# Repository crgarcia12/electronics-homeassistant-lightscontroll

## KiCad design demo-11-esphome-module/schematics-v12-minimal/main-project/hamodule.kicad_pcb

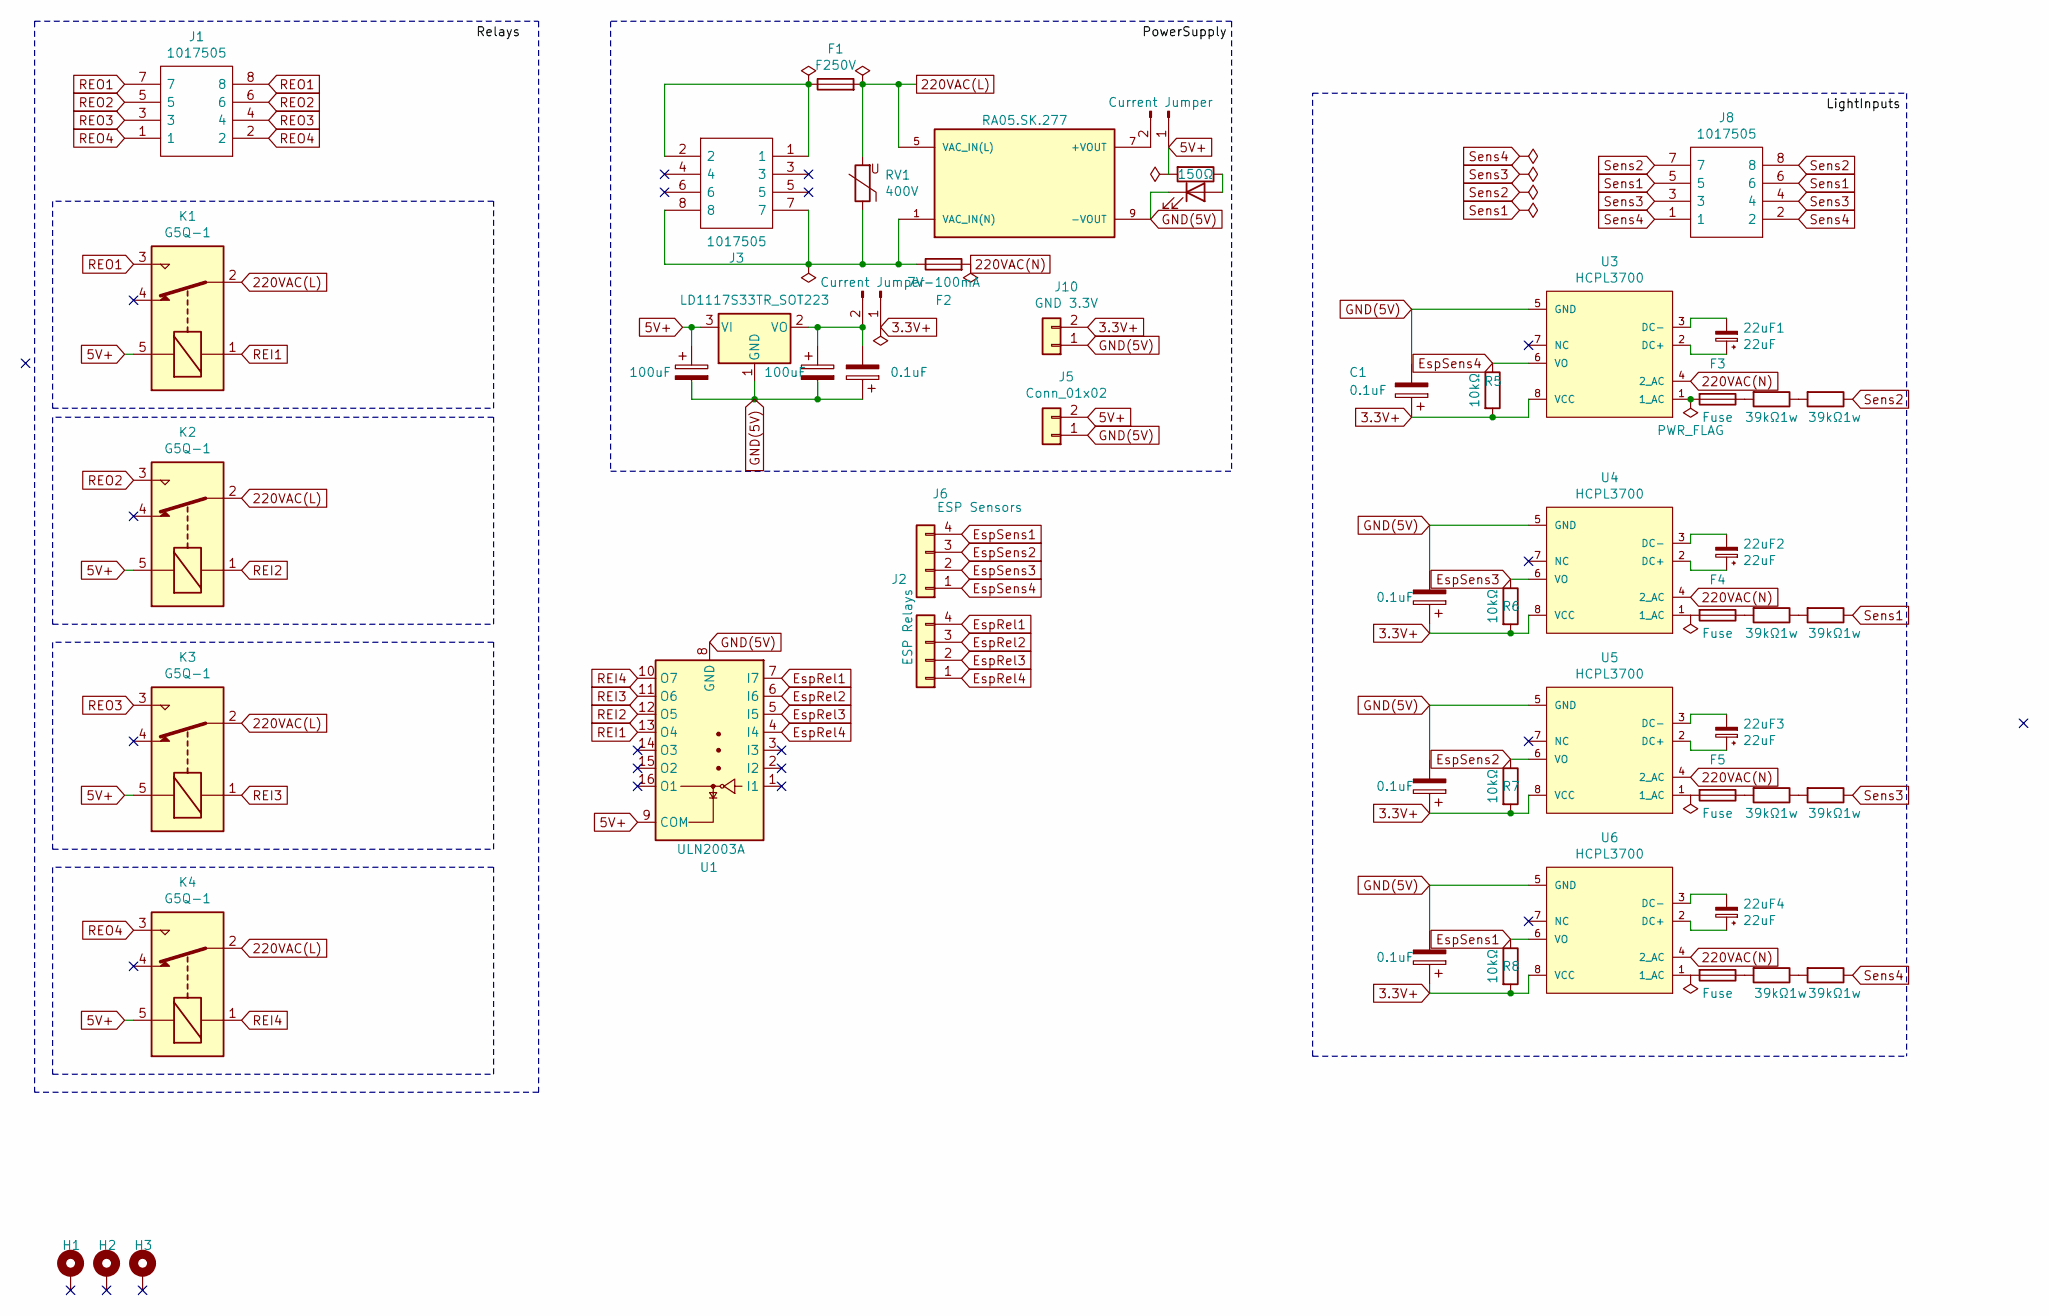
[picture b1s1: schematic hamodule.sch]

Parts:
22uF1, 22uF2, 22uF3, 22uF4: 22uF; CP_EIA-3528-21_Kemet-B_Pad1.50x2.35mm_HandSolder; JLCPCB C110051
100uF_1, 100uF_2: 100uF; CP_Radial_D6.3mm_P2.50mm
C1, C2, C3, C4, C5: 0.1uF; C_0805_2012Metric_Pad1.15x1.40mm_HandSolder; JLCPCB C235777
D9: LED; LED_0805_2012Metric_Pad1.15x1.40mm_HandSolder; JLCPCB C2297
F1: F250V; Fuse_Littelfuse_372_D8.50mm
F2: 7V-100mA; Fuse_Littelfuse_372_D8.50mm
F3, F4, F5, F6: Fuse; Fuse_1812_4532Metric_Pad1.30x3.40mm_HandSolder; JLCPCB C207063
H1, H2, H3: MountingHole_Pad; MountingHole_3.2mm_M3_ISO14580_Pad
J1, J3, J8: 1017505; 1017505_pretty; Manufacturer_Part_Number 1017505; Mouser Part Number 651-1017505
J2: ESP Relays; JST_XH_B4B-XH-A_1x04_P2.50mm_Vertical
J5: Conn_01x02; JST_XH_B2B-XH-A_1x02_P2.50mm_Vertical
J6: ESP Sensors; JST_XH_B4B-XH-A_1x04_P2.50mm_Vertical
J9, J11: Current Jumper; PinHeader_1x02_P2.54mm_Vertical
J10: GND 3.3V; JST_XH_B2B-XH-A_1x02_P2.50mm_Vertical
K1, K2, K3, K4: G5Q-1; Relay_SPDT_Omron-G5Q-1
R5, R6, R7, R8: 10kΩ; R_1206_3216Metric_Pad1.42x1.75mm_HandSolder; JLCPCB C17902
R9: 150Ω; R_0805_2012Metric_Pad1.15x1.40mm_HandSolder; JLCPCB C17471
R10, R11, R12, R13, R14, R15, R16, R17: 39kΩ1w; R_2512_6332Metric_Pad1.52x3.35mm_HandSolder; JLCPCB C25723
RA05.SK.277: RAC05.05SK.277; 277; PARTREV N/A
RV1: 400V; RV_Disc_D12mm_W4.2mm_P7.5mm
U1: ULN2003A; SOIC-16_3.9x9.9mm_P1.27mm; JLCPCB C7512
U2: LD1117S33TR_SOT223; TO-220-3_Vertical
U3, U4, U5, U6: HCPL3700; DIP-8_W7.62mm_Socket_LongPads; Voltage - Isolation 2500Vrms; Voltage - Output (Max) 20V; mouser part number 512-HCPL-3700; digikey description Optoisolator Darlington Output 2500Vrms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

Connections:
3.3V+: C1.1, C2.1, C3.1, C4.1, J10.2, J11.1, R5.2, R6.2, R7.2, R8.2, U3.8 (VCC), U4.8 (VCC), U5.8 (VCC), U6.8 (VCC)
5V+: 100uF_1.1, J5.2, J9.1, K1.5, K2.5, K3.5, K4.5, R9.2, U1.9 (COM), U2.3 (VI); also elsewhere on the board
220VAC(L): F1.2, K1.2, K2.2, K3.2, K4.2, RA05.SK.277.5 (VAC_IN(L)), RV1.2
220VAC(N): F2.2, U3.4 (2_AC), U4.4 (2_AC), U5.4 (2_AC), U6.4 (2_AC)
EspRel1: J2.4, U1.7 (I7)
EspRel2: J2.3, U1.6 (I6)
EspRel3: J2.2, U1.5 (I5)
EspRel4: J2.1, U1.4 (I4)
EspSens1: J6.4, R8.1, U6.6 (VO)
EspSens2: J6.3, R7.1, U5.6 (VO)
EspSens3: J6.2, R6.1, U4.6 (VO)
EspSens4: J6.1, R5.1, U3.6 (VO)
unnamed: 22uF1.1, U3.2 (DC+)
unnamed: 22uF1.2, U3.3 (DC-)
unnamed: 22uF2.1, U4.2 (DC+)
unnamed: 22uF2.2, U4.3 (DC-)
unnamed: 22uF3.1, U5.2 (DC+)
unnamed: 22uF3.2, U5.3 (DC-)
unnamed: 22uF4.1, U6.2 (DC+)
unnamed: 22uF4.2, U6.3 (DC-)
unnamed: D9.2 (A), R9.1
unnamed: F1.1, J3.1, J3.2
unnamed: F2.1, J3.7, J3.8, RA05.SK.277.1 (VAC_IN(N)), RV1.1
unnamed: F3.1, R16.2
unnamed: F3.2, U3.1 (1_AC)
unnamed: F4.1, R14.2
unnamed: F4.2, U4.1 (1_AC)
unnamed: F5.1, R12.2
unnamed: F5.2, U5.1 (1_AC)
unnamed: F6.1, R10.2
unnamed: F6.2, U6.1 (1_AC)
unnamed: J9.2, RA05.SK.277.7 (+VOUT)
unnamed: R10.1, R17.2
unnamed: R11.2, R16.1
unnamed: R12.1, R15.2
unnamed: R13.2, R14.1
REI1: K1.1, U1.13 (O4)
REI2: K2.1, U1.12 (O5)
REI3: K3.1, U1.11 (O6)
REI4: K4.1, U1.10 (O7)
REO1: J1.7, J1.8, K1.3
REO2: J1.5, J1.6, K2.3
REO3: J1.3, J1.4, K3.3
REO4: J1.1, J1.2, K4.3
Sens1: J8.5, J8.6, R13.1
Sens2: J8.7, J8.8, R11.1
Sens3: J8.3, J8.4, R15.1
Sens4: J8.1, J8.2, R17.1

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
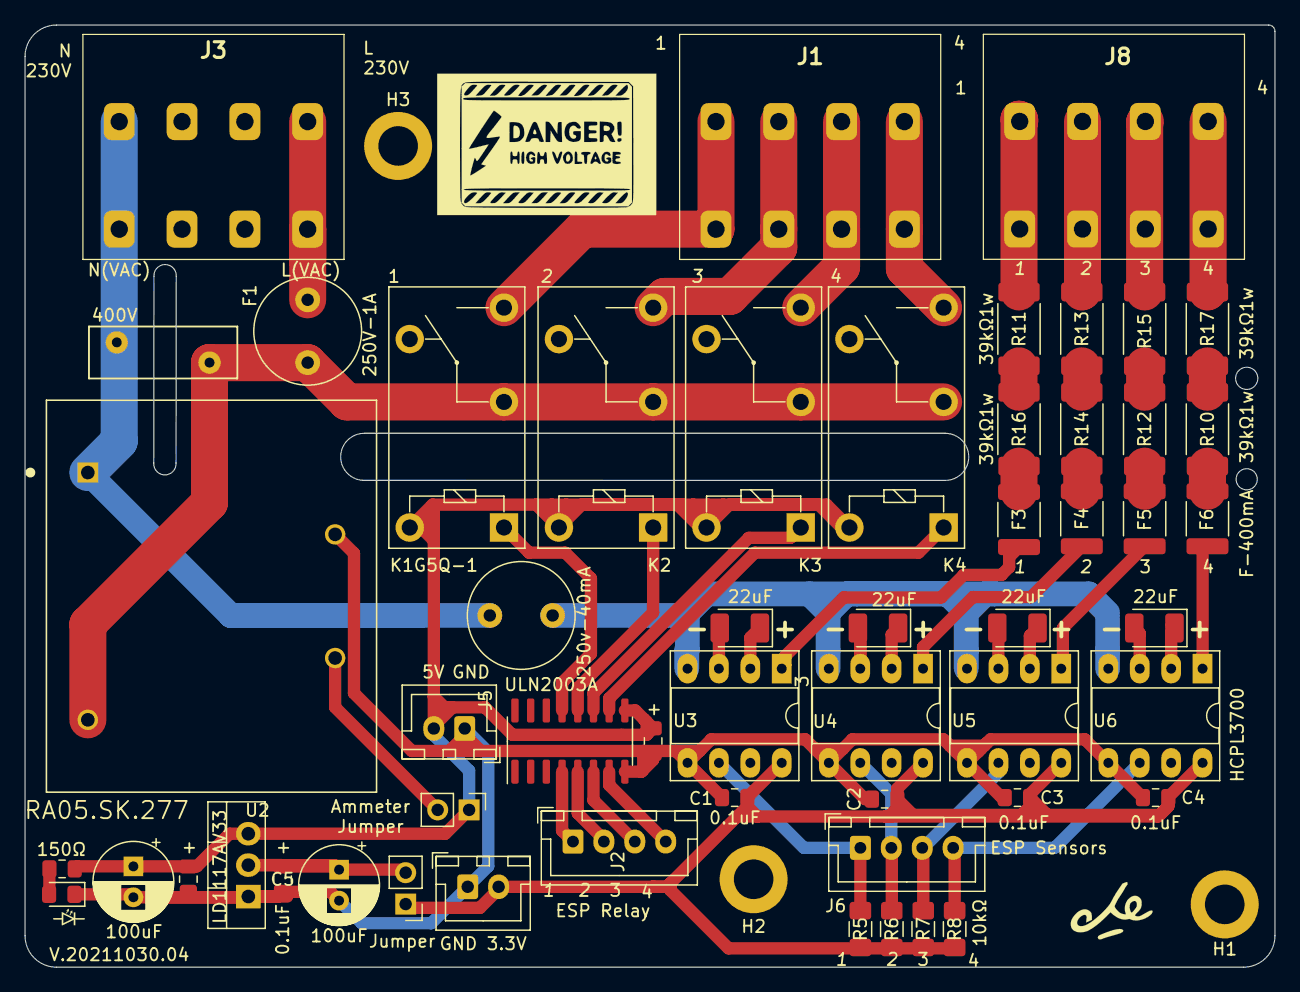
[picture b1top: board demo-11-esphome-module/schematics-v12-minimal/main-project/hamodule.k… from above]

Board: 2 copper layers, 101.1 x 76.2 mm, 57 parts (0 on the bottom side), 50 nets.

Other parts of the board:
C6, C7: 0.1uF; C_0805_2012Metric_Pad1.15x1.40mm_HandSolder

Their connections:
5V+: C6.1, C7.1; also elsewhere on the board

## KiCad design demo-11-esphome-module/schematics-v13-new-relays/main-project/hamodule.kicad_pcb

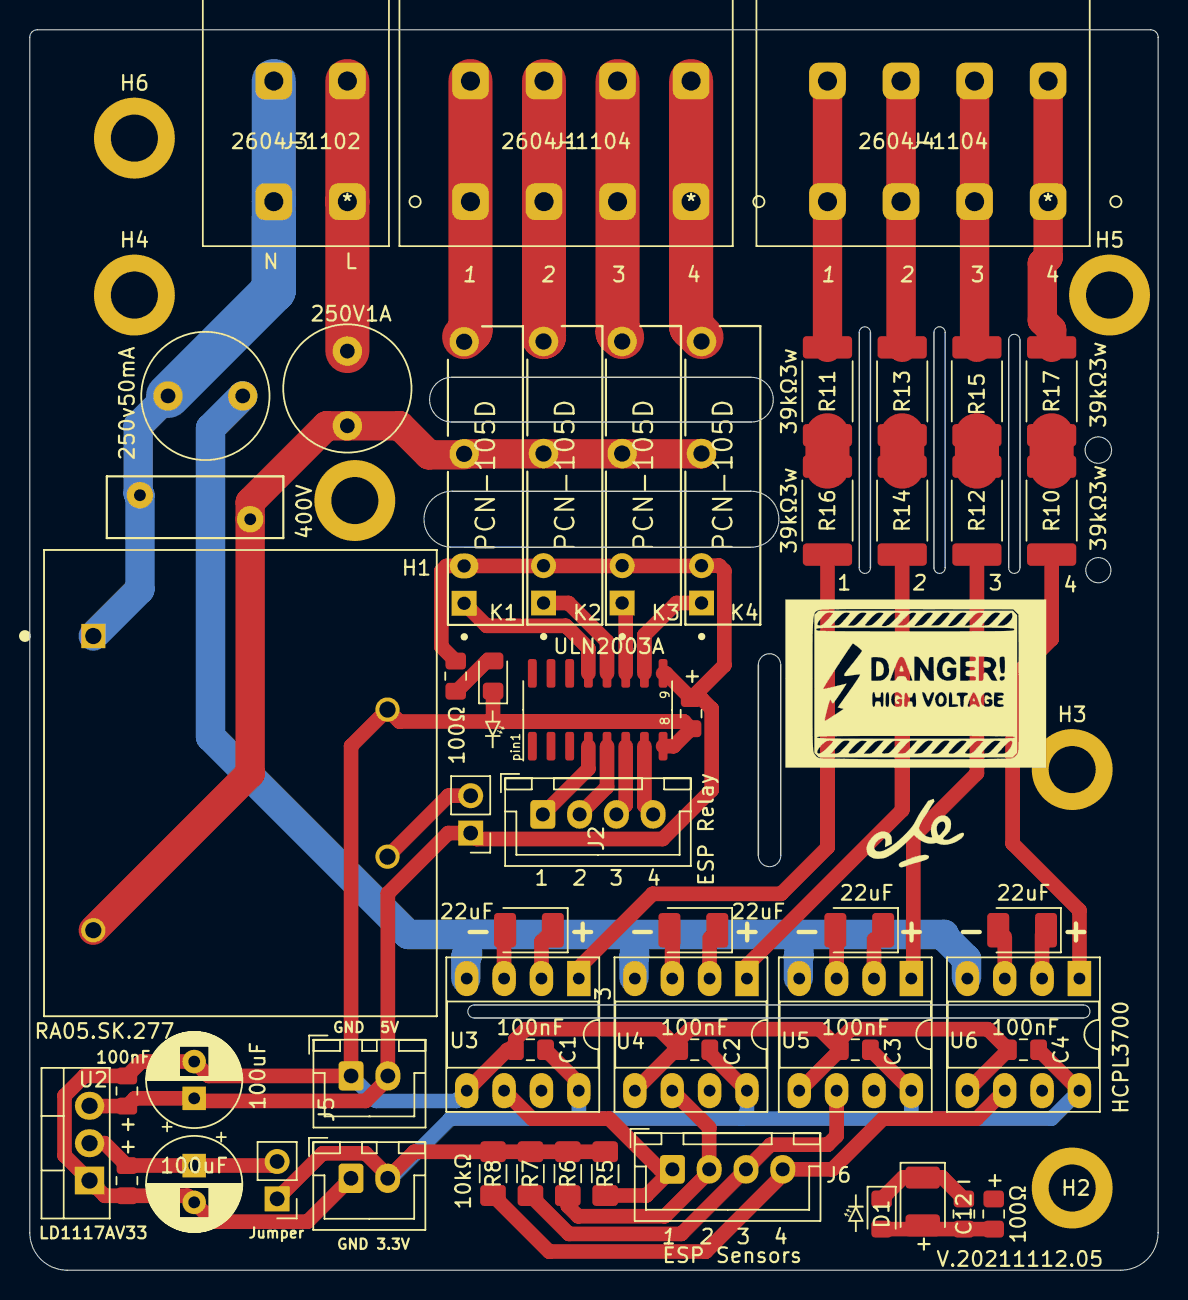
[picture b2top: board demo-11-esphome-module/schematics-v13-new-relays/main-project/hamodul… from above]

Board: 2 copper layers, 76.7 x 84.3 mm, 60 parts (0 on the bottom side), 48 nets.

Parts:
100uF_1, 100uF_2: 100uF; CP_Radial_D6.3mm_P2.50mm
C1, C2, C3, C4, C5, C6, C7, C12: 100nF; C_0805_2012Metric_Pad1.15x1.40mm_HandSolder
C8, C9, C10, C11, C13: 22uF; CP_EIA-3528-21_Kemet-B_Pad1.50x2.35mm_HandSolder
D1, D9: LED; LED_0805_2012Metric_Pad1.15x1.40mm_HandSolder
F1: 250V1A; Fuse_Littelfuse_372_D8.50mm
F2: 250v50mA; Fuse_Littelfuse_372_D8.50mm
H1, H2, H3, H4, H5, H6: MountingHole_Pad; MountingHole_3.2mm_M3_ISO14580_Pad
J1, J4: 2604-1104; big_pads_2604-1104
J2: ESP Relays; JST_XH_B4B-XH-A_1x04_P2.50mm_Vertical
J3: 2604-1102; big_pads_2604-1102
J5: Conn_01x02; JST_XH_B2B-XH-A_1x02_P2.50mm_Vertical
J6: ESP Sensors; JST_XH_B4B-XH-A_1x04_P2.50mm_Vertical
J9, J11: Current Jumper; PinHeader_1x02_P2.54mm_Vertical
J10: GND 3.3V; JST_XH_B2B-XH-A_1x02_P2.50mm_Vertical
K1, K2, K3, K4: PCN-105D; bigpads_TE_Connectivity-PCN-124D
R1, R9: 100Ω; R_0805_2012Metric_Pad1.15x1.40mm_HandSolder
R5, R6, R7, R8: 10kΩ; R_1206_3216Metric_Pad1.42x1.75mm_HandSolder
R10, R11, R12, R13, R14, R15, R16, R17: 39kΩ3w; R_2512_6332Metric_Pad1.52x3.35mm_HandSolder
RA05.SK.277: RAC05.05SK.277; 277
RV1: 400V; RV_Disc_D12mm_W4.2mm_P7.5mm
U1: ULN2003A; SOIC-16_3.9x9.9mm_P1.27mm
U2: LD1117S33TR_SOT223; TO-220-3_Vertical
U3, U4, U5, U6: HCPL3700; DIP-8_W7.62mm_Socket_LongPads

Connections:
3.3V+: C1.1, C2.1, C3.1, C4.1, J10.2, J11.1, R5.2, R6.2, R7.2, R8.2, U3.8, U4.8, U5.8, U6.8
5V+: 100uF_1.1, C6.1, C7.1, J5.2, J9.1, K1.A2, K2.A2, K3.A2, K4.A2, R9.2, U1.9, U2.3
220VAC(L): F1.2, K1.14, K2.14, K3.14, K4.14, RA05.SK.277.5, RV1.2
220VAC(N): F2.2, U3.4, U4.4, U5.4, U6.4
EspRel1: J2.4, U1.7
EspRel2: J2.3, U1.6
EspRel3: J2.2, U1.5
EspRel4: J2.1, U1.4
EspSens1: J6.4, R8.1, U6.6
EspSens2: J6.3, R7.1, U5.6
EspSens3: J6.2, R6.1, U4.6
EspSens4: J6.1, R5.1, U3.6
GND(5V): 100uF_1.2, 100uF_2.2, C1.2, C2.2, C3.2, C4.2, C5.2, C6.2, C7.2, D9.1, J5.1, J10.1, RA05.SK.277.9, U1.8, U2.1, U3.5, U4.5, U5.5, U6.5
L_IN: F1.1, J3.1, J3.2
N_IN: F2.1, J3.3, J3.4, RA05.SK.277.1, RV1.1
unnamed: 100uF_2.1, C5.1, J11.2, U2.2
unnamed: C8.1, U3.2
unnamed: C8.2, U3.3
unnamed: C9.1, U4.2
unnamed: C9.2, U4.3
unnamed: C10.1, U5.2
unnamed: C10.2, U5.3
unnamed: C11.1, U6.2
unnamed: C11.2, U6.3
unnamed: C12.1, C13.2, D1.2, R1.1
unnamed: C12.2, C13.1, D1.1
unnamed: D9.2, R9.1
unnamed: J9.2, RA05.SK.277.7
unnamed: R10.1, R17.2
unnamed: R10.2, U6.1
unnamed: R11.2, R16.1
unnamed: R12.1, R15.2
unnamed: R12.2, U5.1
unnamed: R13.2, R14.1
unnamed: R14.2, U4.1
unnamed: R16.2, U3.1
REI1: K1.A1, U1.13
REI2: K2.A1, U1.12
REI3: K3.A1, U1.11
REI4: K4.A1, U1.10
REO1: J1.7, J1.8, K1.11
REO2: J1.5, J1.6, K2.11
REO3: J1.3, J1.4, K3.11
REO4: J1.1, J1.2, K4.11
Sens1: J4.7, J4.8, R11.1
Sens2: J4.5, J4.6, R13.1
Sens3: J4.3, J4.4, R15.1
Sens4: J4.1, J4.2, R17.1

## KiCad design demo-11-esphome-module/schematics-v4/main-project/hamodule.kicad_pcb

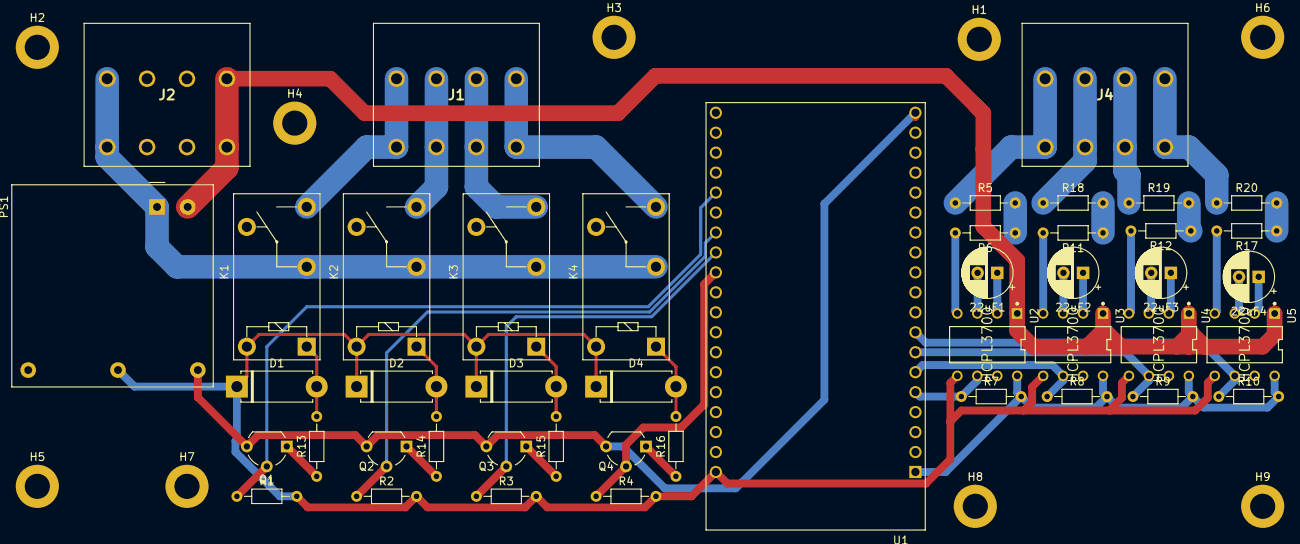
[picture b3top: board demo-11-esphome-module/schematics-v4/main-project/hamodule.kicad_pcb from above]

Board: 2 copper layers, 54 parts (0 on the bottom side), 46 nets.

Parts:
22uF1, 22uF2, 22uF3, 22uF4: CP_Small; CP_Radial_D6.3mm_P2.50mm
D1, D2, D3, D4: DIODE; D_5W_P10.16mm_Horizontal
H1, H2, H3, H4, H5, H6, H7, H8, H9: MountingHole_Pad; MountingHole_3.2mm_M3_ISO14580_Pad
J1, J2, J4: 1017505
K1, K2, K3, K4: G5Q-1; Relay_SPDT_Omron-G5Q-1
PS1: RAC05-05SK; Converter_ACDC_RECOM_RAC05-xxSK_THT
Q1, Q2, Q3, Q4: 2N2219; TO-92_Wide
R1, R2, R3, R4, R7, R8, R9, R10: 10K; R_Axial_DIN0204_L3.6mm_D1.6mm_P7.62mm_Horizontal
R5, R6, R11, R12, R17, R18, R19, R20: 47k; R_Axial_DIN0204_L3.6mm_D1.6mm_P7.62mm_Horizontal
R13, R14, R15, R16: 220; R_Axial_DIN0204_L3.6mm_D1.6mm_P7.62mm_Horizontal
U1: ESP32-DEVKITC-32D; MODULE_ESP32-DEVKITC-32D
U2, U3, U4, U5: HCPL3700; ON_Semi-CASE_62605_ISSUE_P-0-0-0

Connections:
3.3V+: R7.2, R8.2, R9.2, R10.2, U1.1, U2.8, U3.8, U4.8, U5.8
5V+: PS1.5, Q1.3, Q2.3, Q3.3, Q4.3, U1.19
5VGND: D1.1, D2.1, D3.1, D4.1, K1.5, K2.5, K3.5, K4.5, PS1.4, R1.2, R2.2, R3.2, R4.2, U1.20, U2.5, U3.5, U4.5, U5.5
220VAC(L): J2.7, J2.8, K1.2, K2.2, K3.2, K4.2, PS1.1
220VAC(N): J2.1, J2.2, PS1.2, U2.1, U3.1, U4.1, U5.1
Earth: H1.1, H2.1, H3.1, H4.1, H5.1, H6.1, H7.1, H8.1, H9.1, J2.3, J2.4, J2.5, J2.6
GPIO32: R9.1, U1.7, U4.6
GPIO33: R10.1, U1.8, U5.6
GPIO34: R7.1, U1.5, U2.6
GPIO35: R8.1, U1.6, U3.6
unnamed: 22uF1.1, U2.2
unnamed: 22uF1.2, U2.3
unnamed: 22uF2.1, U3.2
unnamed: 22uF2.2, U3.3
unnamed: 22uF3.1, U4.2
unnamed: 22uF3.2, U4.3
unnamed: 22uF4.1, U5.2
unnamed: 22uF4.2, U5.3
unnamed: D1.2, K1.1, R13.2
unnamed: D2.2, K2.1, R14.2
unnamed: D3.2, K3.1, R15.2
unnamed: D4.2, K4.1, R16.2
unnamed: Q1.1, R13.1
unnamed: Q1.2, R1.1, U1.34
unnamed: Q2.1, R14.1
unnamed: Q2.2, R2.1, U1.32
unnamed: Q3.1, R15.1
unnamed: Q3.2, R3.1, U1.31
unnamed: Q4.1, R16.1
unnamed: Q4.2, R4.1, U1.30
unnamed: R5.2, R6.1
unnamed: R6.2, U2.4
unnamed: R11.1, R18.2
unnamed: R11.2, U3.4
unnamed: R12.1, R19.2
unnamed: R12.2, U4.4
unnamed: R17.1, R20.2
unnamed: R17.2, U5.4
REO1: J1.7, J1.8, K1.3
REO2: J1.5, J1.6, K2.3
REO3: J1.3, J1.4, K3.3
REO4: J1.1, J1.2, K4.3
Sens1: J4.7, J4.8, R5.1
Sens2: J4.5, J4.6, R18.1
Sens3: J4.3, J4.4, R19.1
Sens4: J4.1, J4.2, R20.1

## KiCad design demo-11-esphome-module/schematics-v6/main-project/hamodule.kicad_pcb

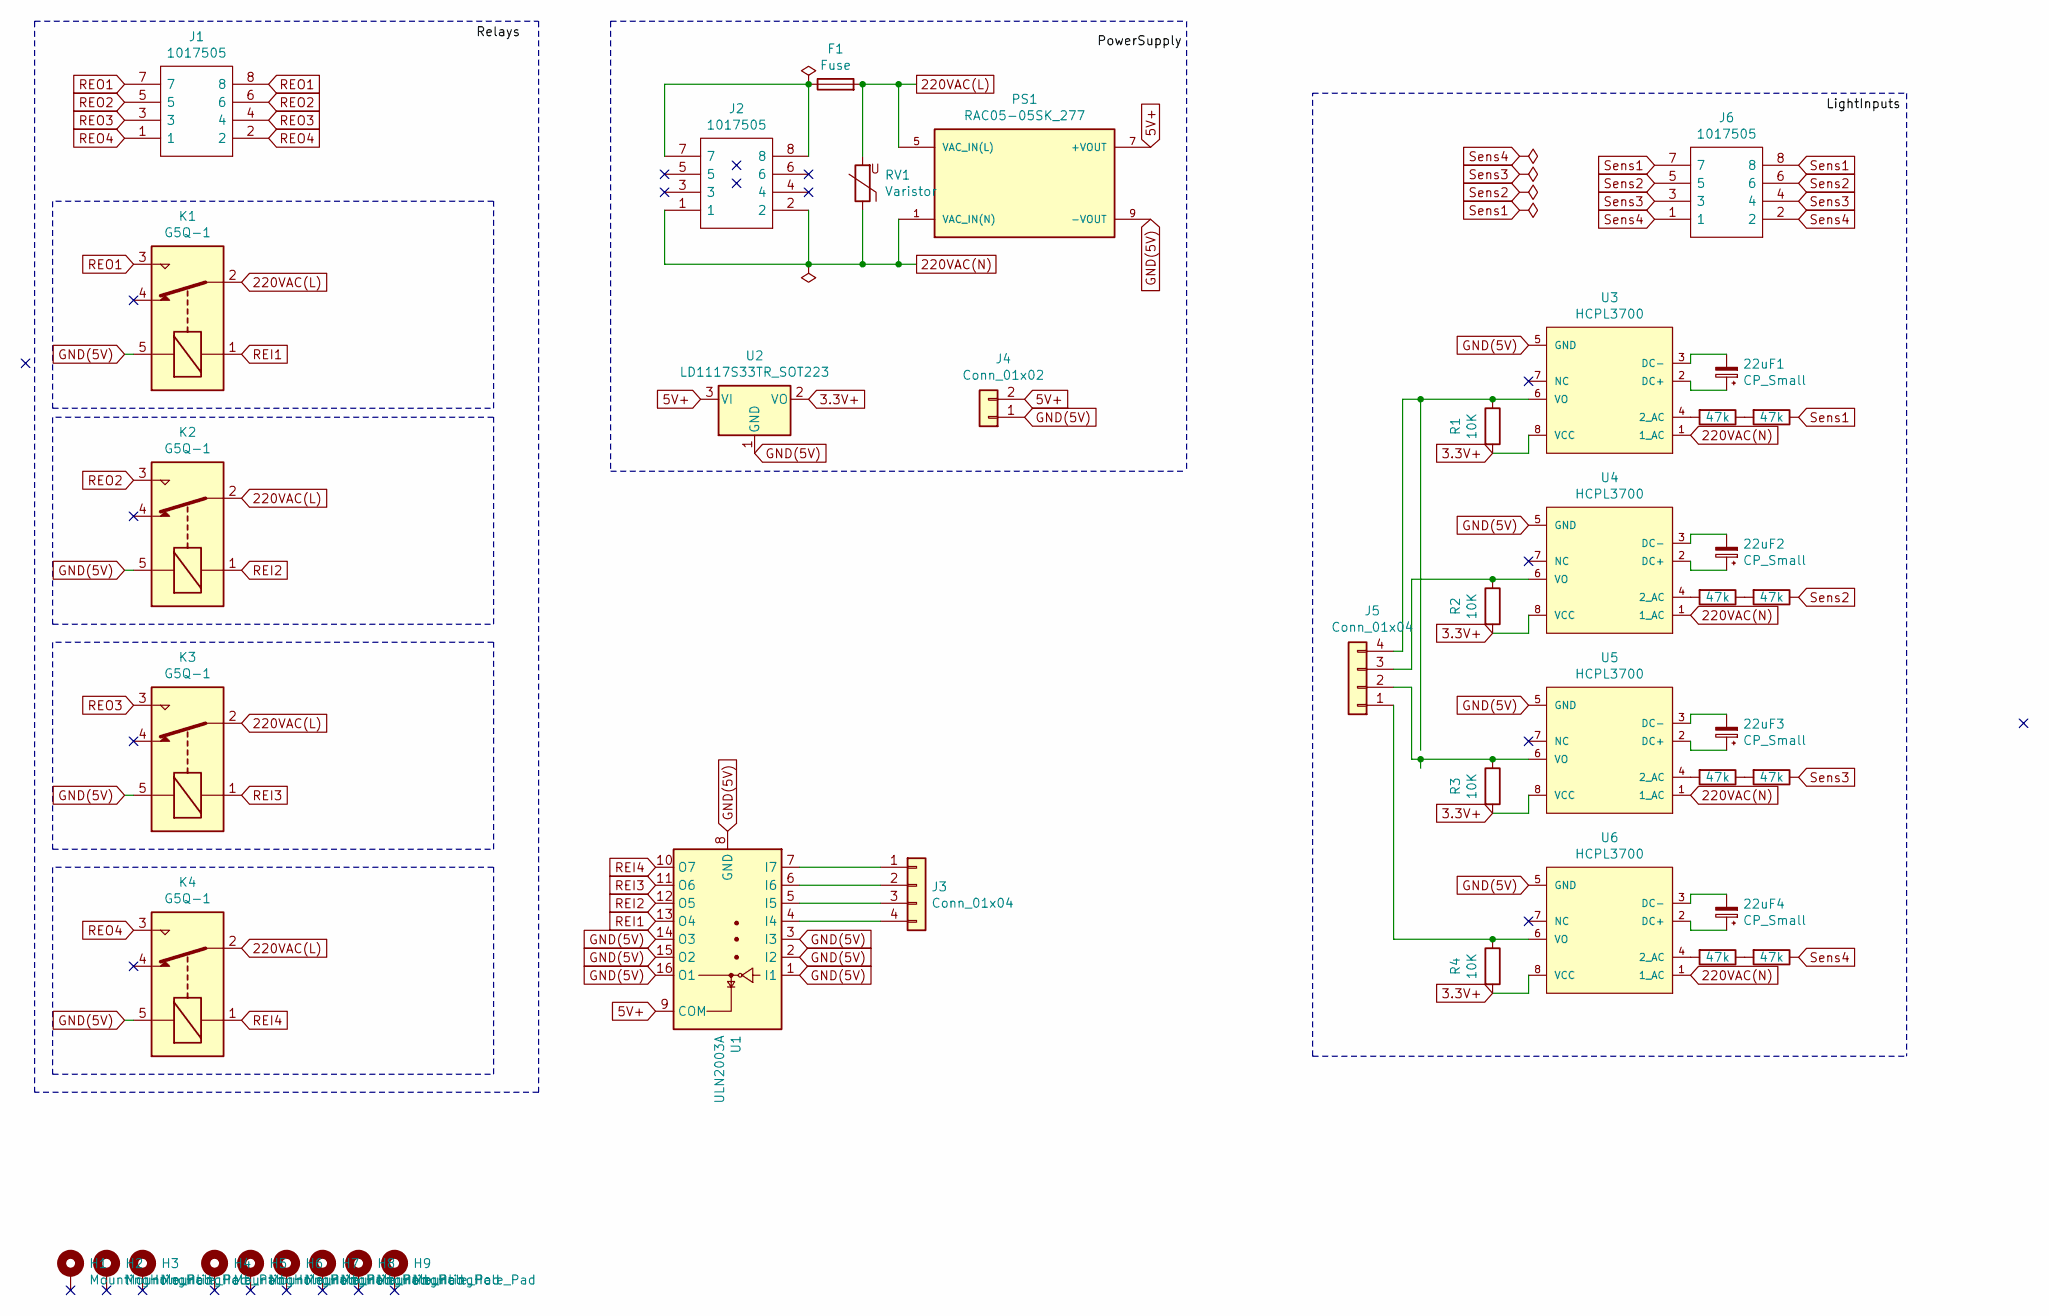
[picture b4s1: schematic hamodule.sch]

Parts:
22uF1, 22uF2, 22uF3, 22uF4: CP_Small; CP_Radial_D17.0mm_P7.50mm
F1: Fuse; Fuse_Littelfuse_372_D8.50mm
H1, H2, H3, H4, H5, H6, H7, H8, H9: MountingHole_Pad; MountingHole_3.2mm_M3_ISO14580_Pad
J1, J2, J6: 1017505; Manufacturer_Part_Number 1017505; Mouser Part Number 651-1017505
J3, J5: Conn_01x04; Molex_KK-396_A-41791-0004_1x04_P3.96mm_Vertical
J4: Conn_01x02; Molex_KK-396_A-41791-0002_1x02_P3.96mm_Vertical
K1, K2, K3, K4: G5Q-1; Relay_SPDT_Omron-G5Q-1
PS1: RAC05-05SK_277; 277; PARTREV N/A
R1, R2, R3, R4: 10K; R_Axial_DIN0204_L3.6mm_D1.6mm_P7.62mm_Horizontal
R5, R6, R7, R8: 47k; R_Axial_DIN0516_L15.5mm_D5.0mm_P20.32mm_Horizontal
R9, R10, R11, R12: 47k; R_Axial_DIN0516_L15.5mm_D5.0mm_P5.08mm_Vertical
RV1: Varistor; RV_Disc_D21.5mm_W5.3mm_P10mm
U1: ULN2003A; DIP-16_W7.62mm_LongPads
U2: LD1117S33TR_SOT223; TO-218-3_Vertical
U3, U4, U5, U6: HCPL3700; ON_Semi-CASE_62605_ISSUE_P-0-0-0; Voltage - Isolation 2500Vrms; Voltage - Output (Max) 20V; mouser part number 512-HCPL-3700; digikey description Optoisolator Darlington Output 2500Vrms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

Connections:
3.3V+: R1.2, R2.2, R3.2, R4.2, U2.2 (VO), U3.8 (VCC), U4.8 (VCC), U5.8 (VCC), U6.8 (VCC)
5V+: J4.2, PS1.7 (+VOUT), U1.9 (COM), U2.3 (VI)
220VAC(L): F1.2, K1.2, K2.2, K3.2, K4.2, PS1.5 (VAC_IN(L)), RV1.2
220VAC(N): J2.1, J2.2, PS1.1 (VAC_IN(N)), RV1.1, U3.1 (1_AC), U4.1 (1_AC), U5.1 (1_AC), U6.1 (1_AC)
GND(5V): J4.1, K1.5, K2.5, K3.5, K4.5, PS1.9 (-VOUT), U1.1 (I1), U1.2 (I2), U1.3 (I3), U1.8 (GND), U1.14 (O3), U1.15 (O2), U1.16 (O1), U2.1 (GND), U3.5 (GND), U4.5 (GND), U5.5 (GND), U6.5 (GND)
unnamed: 22uF1.1, U3.2 (DC+)
unnamed: 22uF1.2, U3.3 (DC-)
unnamed: 22uF2.1, U4.2 (DC+)
unnamed: 22uF2.2, U4.3 (DC-)
unnamed: 22uF3.1, U5.2 (DC+)
unnamed: 22uF3.2, U5.3 (DC-)
unnamed: 22uF4.1, U6.2 (DC+)
unnamed: 22uF4.2, U6.3 (DC-)
unnamed: F1.1, J2.7, J2.8
unnamed: J3.1, U1.7 (I7)
unnamed: J3.2, U1.6 (I6)
unnamed: J3.3, U1.5 (I5)
unnamed: J3.4, U1.4 (I4)
unnamed: J5.1, R4.1, U6.6 (VO)
unnamed: J5.2, R3.1, U5.6 (VO)
unnamed: J5.3, R2.1, U4.6 (VO)
unnamed: J5.4, R1.1, U3.6 (VO)
unnamed: R5.1, R9.2
unnamed: R5.2, U3.4 (2_AC)
unnamed: R6.2, U4.4 (2_AC)
unnamed: R7.2, U5.4 (2_AC)
unnamed: R8.2, U6.4 (2_AC)
unnamed: R6.1, R10.2
unnamed: R7.1, R11.2
unnamed: R8.1, R12.2
REI1: K1.1, U1.13 (O4)
REI2: K2.1, U1.12 (O5)
REI3: K3.1, U1.11 (O6)
REI4: K4.1, U1.10 (O7)
REO1: J1.7, J1.8, K1.3
REO2: J1.5, J1.6, K2.3
REO3: J1.3, J1.4, K3.3
REO4: J1.1, J1.2, K4.3
Sens1: J6.7, J6.8, R9.1
Sens2: J6.5, J6.6, R10.1
Sens3: J6.3, J6.4, R11.1
Sens4: J6.1, J6.2, R12.1

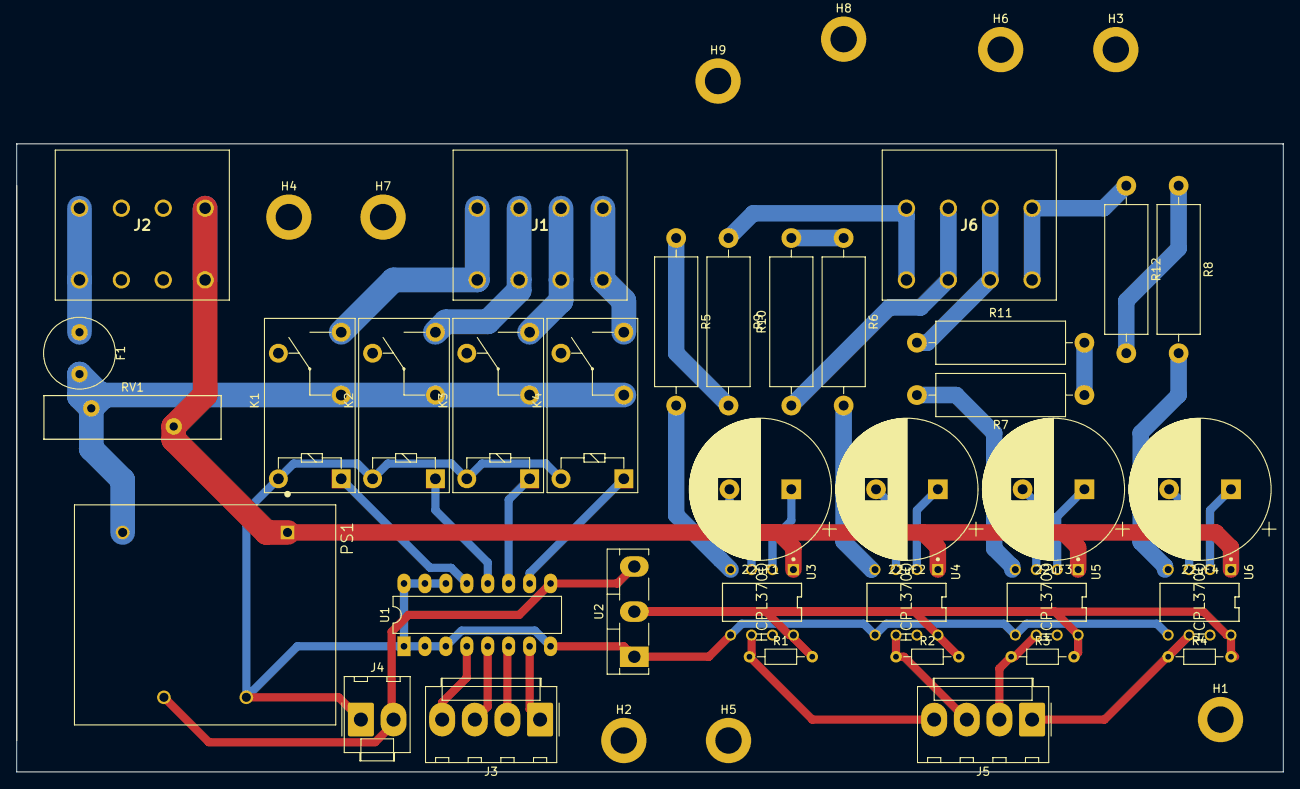
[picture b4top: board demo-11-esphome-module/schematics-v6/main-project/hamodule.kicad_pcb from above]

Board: 2 copper layers, 153.7 x 76.2 mm, 44 parts (0 on the bottom side), 42 nets.

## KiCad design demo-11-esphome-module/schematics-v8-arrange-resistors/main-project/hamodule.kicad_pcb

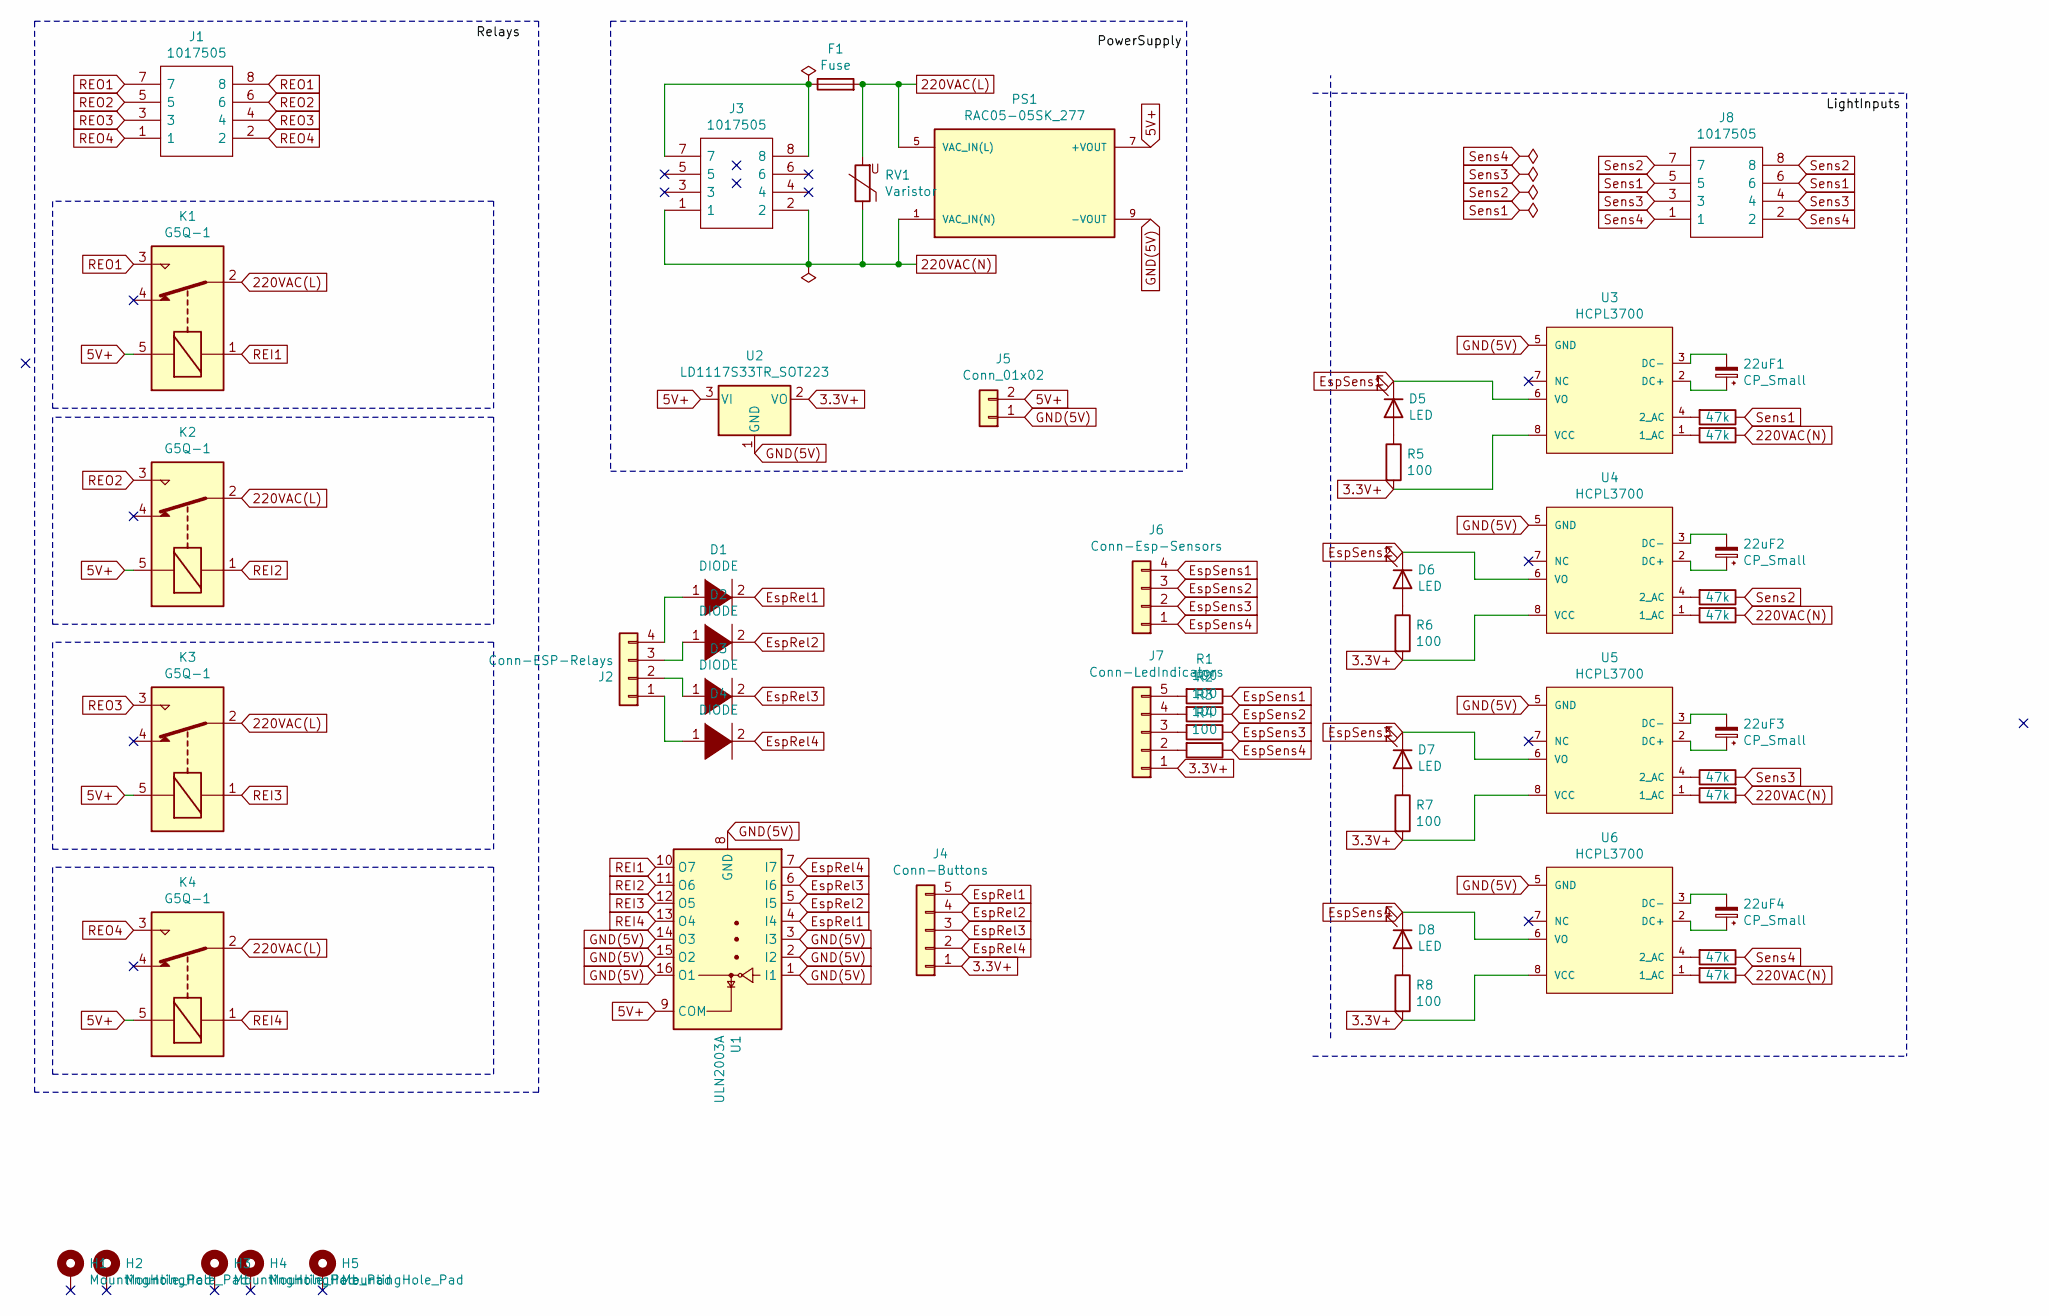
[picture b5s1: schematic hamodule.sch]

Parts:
22uF1, 22uF2, 22uF3, 22uF4: CP_Small; CP_Radial_D10.0mm_P5.00mm
D1, D2, D3, D4: DIODE; D_DO-35_SOD27_P7.62mm_Horizontal
D5, D6, D7, D8: LED; LED_D3.0mm
F1: Fuse; Fuse_Littelfuse_372_D8.50mm
H1, H2, H3, H4, H5: MountingHole_Pad; MountingHole_3.2mm_M3_ISO14580_Pad
J1, J3, J8: 1017505; Manufacturer_Part_Number 1017505; Mouser Part Number 651-1017505
J2: Conn-ESP-Relays; JST_XH_B4B-XH-A_1x04_P2.50mm_Vertical
J4: Conn-Buttons; JST_XH_B5B-XH-A_1x05_P2.50mm_Vertical
J5: Conn_01x02; JST_XH_B2B-XH-A_1x02_P2.50mm_Vertical
J6: Conn-Esp-Sensors; JST_XH_B4B-XH-A_1x04_P2.50mm_Vertical
J7: Conn-LedIndicators; JST_XH_B5B-XH-A_1x05_P2.50mm_Vertical
K1, K2, K3, K4: G5Q-1; Relay_SPDT_Omron-G5Q-1
PS1: RAC05-05SK_277; 277; PARTREV N/A
R1, R2, R3, R4, R5, R6, R7, R8: 100; R_Axial_DIN0207_L6.3mm_D2.5mm_P7.62mm_Horizontal
R9, R10, R11, R12, R13, R14, R15, R16: 47k; R_Axial_DIN0516_L15.5mm_D5.0mm_P20.32mm_Horizontal
RV1: Varistor; RV_Disc_D21.5mm_W5.3mm_P10mm
U1: ULN2003A; DIP-16_W7.62mm_LongPads
U2: LD1117S33TR_SOT223; TO-220-3_Vertical
U3, U4, U5, U6: HCPL3700; DIP-8_W7.62mm_Socket_LongPads; Voltage - Isolation 2500Vrms; Voltage - Output (Max) 20V; mouser part number 512-HCPL-3700; digikey description Optoisolator Darlington Output 2500Vrms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

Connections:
3.3V+: J4.1, J7.1, R5.2, R6.2, R7.2, R8.2, U2.2 (VO), U3.8 (VCC), U4.8 (VCC), U5.8 (VCC), U6.8 (VCC)
5V+: J5.2, K1.5, K2.5, K3.5, K4.5, PS1.7 (+VOUT), U1.9 (COM), U2.3 (VI)
220VAC(L): F1.2, K1.2, K2.2, K3.2, K4.2, PS1.5 (VAC_IN(L)), RV1.2
220VAC(N): J3.1, J3.2, PS1.1 (VAC_IN(N)), R10.1, R12.1, R14.2, R16.1, RV1.1
EspRel1: D1.2 (A), J4.5, U1.4 (I4)
EspRel2: D2.2 (A), J4.4, U1.5 (I5)
EspRel3: D3.2 (A), J4.3, U1.6 (I6)
EspRel4: D4.2 (A), J4.2, U1.7 (I7)
EspSens1: D5.1 (K), J6.4, R1.1, U3.6 (VO)
EspSens2: D6.1 (K), J6.3, R2.1, U4.6 (VO)
EspSens3: D7.1 (K), J6.2, R3.1, U5.6 (VO)
EspSens4: D8.1 (K), J6.1, R4.1, U6.6 (VO)
GND(5V): J5.1, PS1.9 (-VOUT), U1.1 (I1), U1.2 (I2), U1.3 (I3), U1.8 (GND), U1.14 (O3), U1.15 (O2), U1.16 (O1), U2.1 (GND), U3.5 (GND), U4.5 (GND), U5.5 (GND), U6.5 (GND)
unnamed: 22uF1.1, U3.2 (DC+)
unnamed: 22uF1.2, U3.3 (DC-)
unnamed: 22uF2.1, U4.2 (DC+)
unnamed: 22uF2.2, U4.3 (DC-)
unnamed: 22uF3.1, U5.2 (DC+)
unnamed: 22uF3.2, U5.3 (DC-)
unnamed: 22uF4.1, U6.2 (DC+)
unnamed: 22uF4.2, U6.3 (DC-)
unnamed: D1.1 (K), J2.4
unnamed: D2.1 (K), J2.3
unnamed: D3.1 (K), J2.2
unnamed: D4.1 (K), J2.1
unnamed: D5.2 (A), R5.1
unnamed: D6.2 (A), R6.1
unnamed: D7.2 (A), R7.1
unnamed: D8.2 (A), R8.1
unnamed: F1.1, J3.7, J3.8
unnamed: J7.2, R4.2
unnamed: J7.3, R3.2
unnamed: J7.4, R2.2
unnamed: J7.5, R1.2
unnamed: R9.2, U3.4 (2_AC)
unnamed: R10.2, U3.1 (1_AC)
unnamed: R11.2, U4.4 (2_AC)
unnamed: R12.2, U4.1 (1_AC)
unnamed: R13.1, U5.4 (2_AC)
unnamed: R14.1, U5.1 (1_AC)
unnamed: R15.2, U6.4 (2_AC)
unnamed: R16.2, U6.1 (1_AC)
REI1: K1.1, U1.10 (O7)
REI2: K2.1, U1.11 (O6)
REI3: K3.1, U1.12 (O5)
REI4: K4.1, U1.13 (O4)
REO1: J1.7, J1.8, K1.3
REO2: J1.5, J1.6, K2.3
REO3: J1.3, J1.4, K3.3
REO4: J1.1, J1.2, K4.3
Sens1: J8.5, J8.6, R9.1
Sens2: J8.7, J8.8, R11.1
Sens3: J8.3, J8.4, R13.2
Sens4: J8.1, J8.2, R15.1

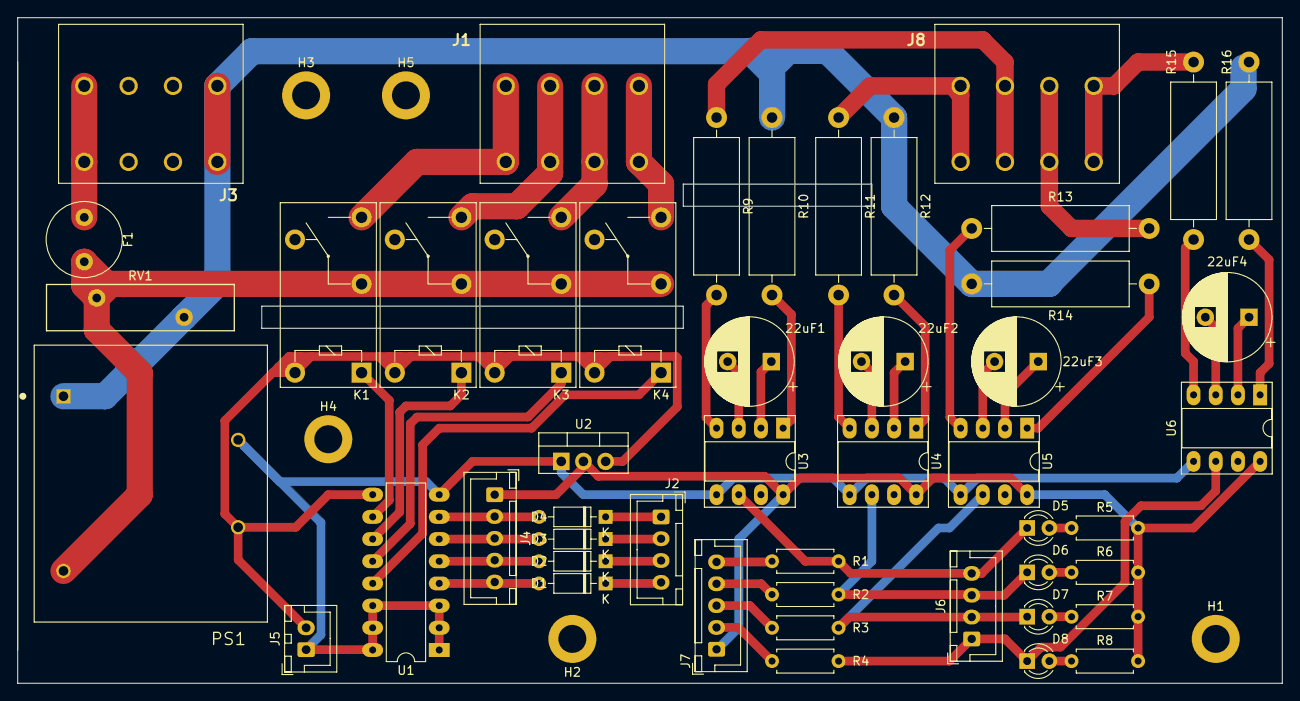
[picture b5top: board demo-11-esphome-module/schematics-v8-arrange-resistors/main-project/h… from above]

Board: 2 copper layers, 144.8 x 76.2 mm, 54 parts (0 on the bottom side), 54 nets.

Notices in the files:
parts and their libraries:
Copyright 2021 Accelerated Designs. All rights reserved.
